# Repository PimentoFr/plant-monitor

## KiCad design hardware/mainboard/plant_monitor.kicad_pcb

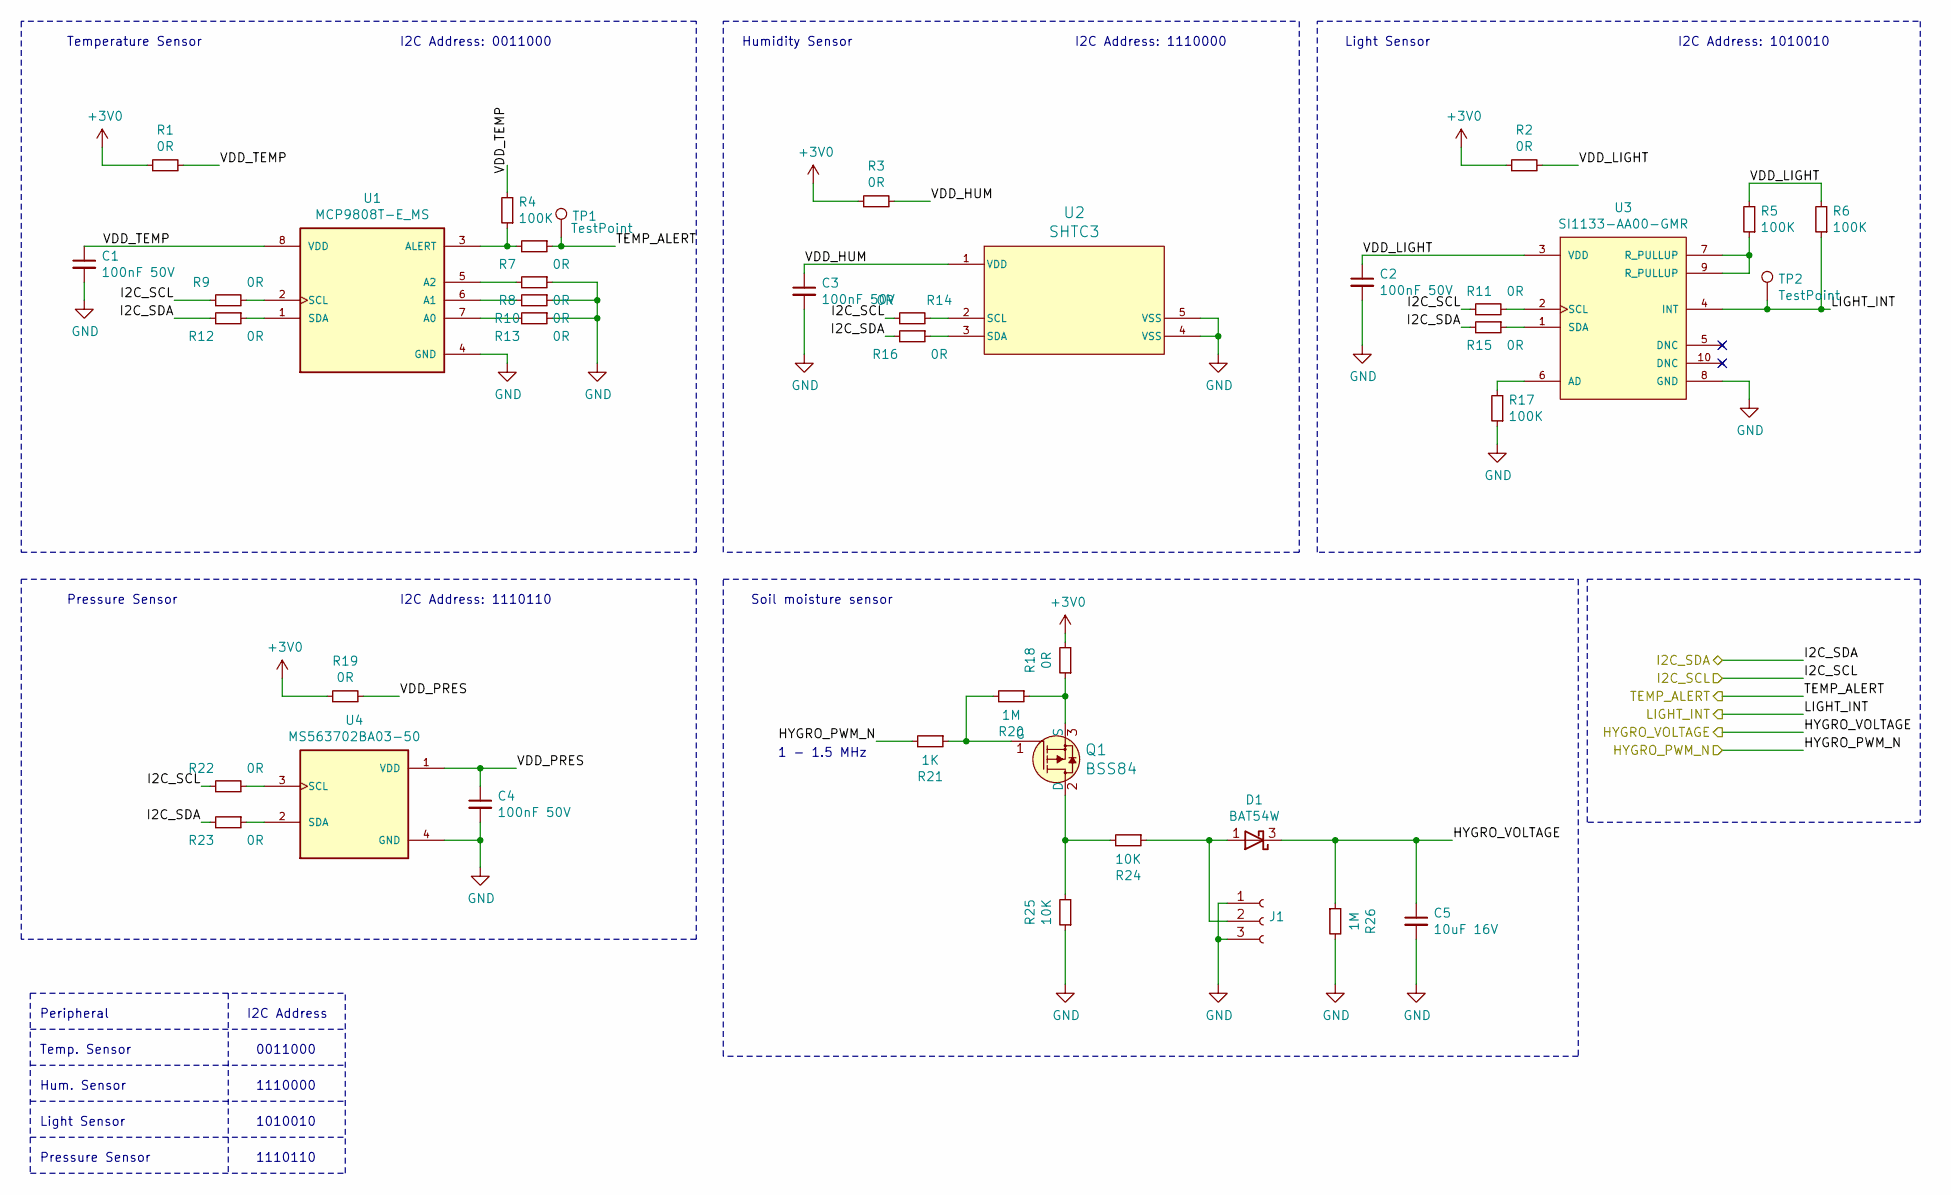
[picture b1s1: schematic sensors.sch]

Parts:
C1, C2, C3, C4: 100nF 50V; C_0402_1005Metric
C5: 10uF 16V; C_0805_2012Metric_Pad1.15x1.40mm_HandSolder; farnell 3013487
D1: BAT54W; SOT-323_SC-70; farnell 1081197
J1: Conn_01x03_Female; PinSocket_1x03_P2.54mm_Vertical
Q1: BSS84; SOT-23-3; MPN BSS84; Digi-Key_PN BSS84CT-ND
R1, R2, R3, R7, R8, R9, R10, R11, R12, R13, R14, R15, R16, R18, R19, R22, R23: 0R; R_0402_1005Metric
R4, R5, R6, R17: 100K; R_0402_1005Metric
R20, R26: 1M; R_0402_1005Metric
R21: 1K; R_0402_1005Metric
R24, R25: 10K; R_0402_1005Metric
TP1, TP2: TestPoint; TestPoint_Pad_D1.0mm
U1: MCP9808T-E_MS; SOP65P490X110-8N; farnell 2851677
U2: SHTC3; farnell 3106918
U3: SI1133-AA00-GMR; farnell 3105966
U4: MS563702BA03-50; TE_MS563702BA03-50; farnell 2362663

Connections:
+3V0: R1.1, R2.1, R3.1, R18.2, R19.1; also elsewhere on the board
/mcu/HYGRO_PWM_N: R21.2; also elsewhere on the board
/mcu/HYGRO_VOLTAGE: C5.1, D1.3 (K), R26.1; also elsewhere on the board
/mcu/I2C_SCL: R9.1, R11.1, R14.1, R22.1; also elsewhere on the board
/mcu/I2C_SDA: R12.2, R15.2, R16.2, R23.2; also elsewhere on the board
/mcu/LIGHT_INT: R6.1, TP2.1, U3.4 (INT); also elsewhere on the board
/mcu/TEMP_ALERT: R7.1, TP1.1; also elsewhere on the board
/sensors/VDD_HUM: C3.1, R3.2, U2.1 (VDD)
/sensors/VDD_LIGHT: C2.1, R2.2, R5.2, R6.2, U3.3 (VDD)
/sensors/VDD_PRES: C4.1, R19.2, U4.1 (VDD)
/sensors/VDD_TEMP: C1.1, R1.2, R4.2, U1.8 (VDD)
GND: C1.2, C2.2, C3.2, C4.2, C5.2, J1.1, J1.3, R8.1, R10.1, R13.1, R17.1, R25.1, R26.2, U1.4 (GND), U2.4 (VSS), U2.5 (VSS), U3.8 (GND), U4.4 (GND); also elsewhere on the board
unnamed: D1.1 (A), J1.2, R24.1
unnamed: Q1.1 (G), R20.2, R21.1
unnamed: Q1.2 (D), R24.2, R25.2
unnamed: Q1.3 (S), R18.1, R20.1
unnamed: R4.1, R7.2, U1.3 (ALERT)
unnamed: R5.1, U3.7 (R_PULLUP), U3.9 (R_PULLUP)
unnamed: R8.2, U1.5 (A2)
unnamed: R9.2, U1.2 (SCL)
unnamed: R10.2, U1.6 (A1)
unnamed: R11.2, U3.2 (SCL)
unnamed: R12.1, U1.1 (SDA)
unnamed: R13.2, U1.7 (A0)
unnamed: R14.2, U2.2 (SCL)
unnamed: R15.1, U3.1 (SDA)
unnamed: R16.1, U2.3 (SDA)
unnamed: R17.2, U3.6 (AD)
unnamed: R22.2, U4.3 (SCL)
unnamed: R23.1, U4.2 (SDA)

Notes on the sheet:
Temperature Sensor
I2C Address: 0011000
I2C Address
Peripheral
Temp. Sensor
0011000
Humidity Sensor
I2C Address: 1110000
Hum. Sensor
1110000
Light Sensor
I2C Address: 1010010
1010010
Pressure Sensor
I2C Address: 1110110
1110110
Soil moisture sensor
1 - 1.5 MHz

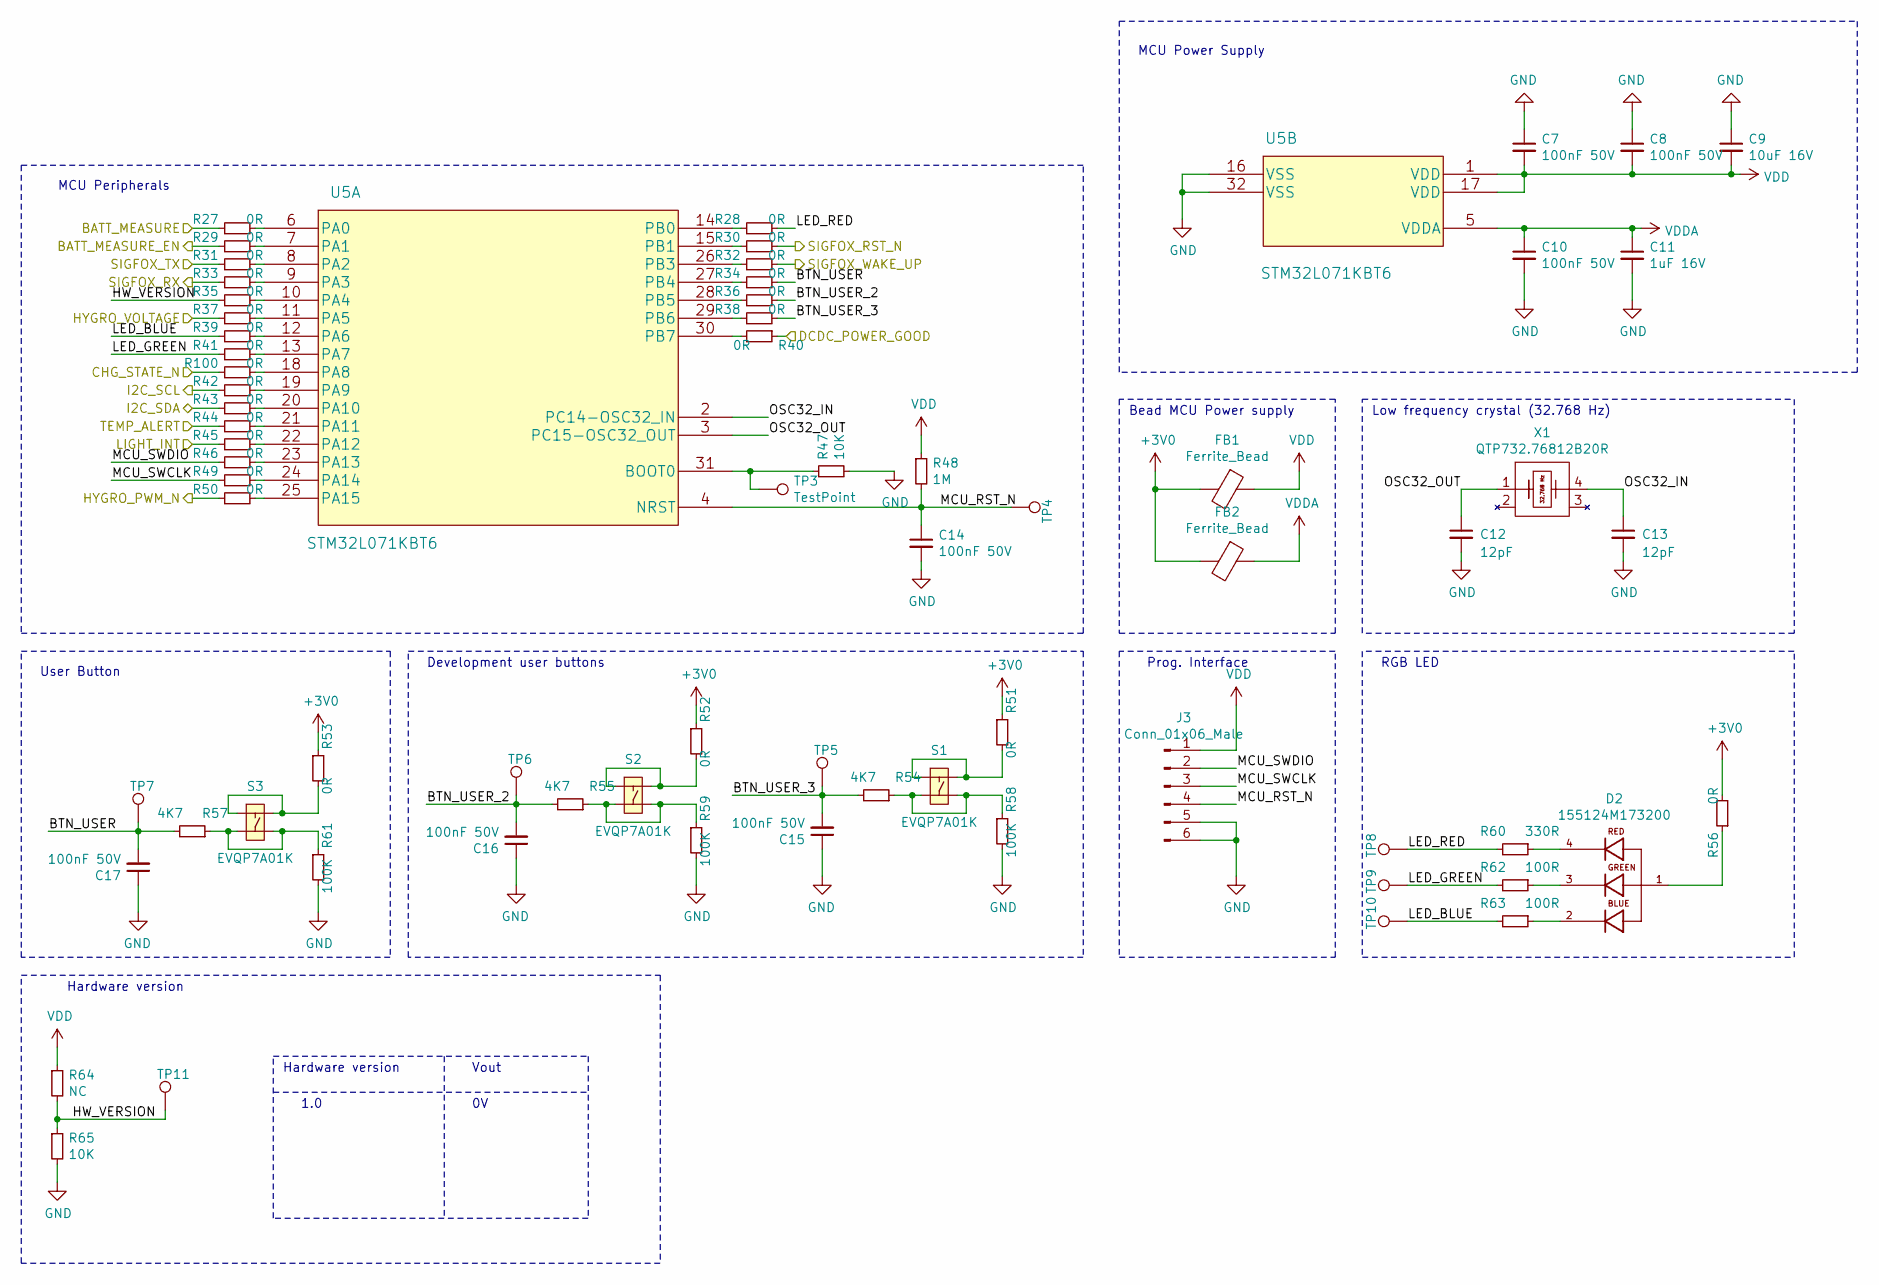
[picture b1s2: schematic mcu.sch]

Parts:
C7, C8, C10, C14, C15, C16, C17: 100nF 50V; C_0402_1005Metric
C9: 10uF 16V; C_0805_2012Metric_Pad1.15x1.40mm_HandSolder; farnell 3013487
C11: 1uF 16V; C_0603_1608Metric; farnell 3013385
C12, C13: 12pF; C_0402_1005Metric
D2: 155124M173200; LED_155124M173200; PARTREV 001.000; farnell 2764995
FB1, FB2: Ferrite_Bead; R_0402_1005Metric
J3: Conn_01x06_Male; PinHeader_1x06_P2.54mm_Vertical; farnell 1593415
R27, R28, R29, R30, R31, R32, R33, R34, R35, R36, R37, R38, R39, R40, R41, R42, R43, R44, R45, R46, R49, R50, R51, R52, R53, R56, R100: 0R; R_0402_1005Metric
R47, R65: 10K; R_0402_1005Metric
R48: 1M; R_0402_1005Metric
R54, R55, R57: 4K7; R_0402_1005Metric
R58, R59, R61: 100K; R_0402_1005Metric
R60: 330R; R_0402_1005Metric
R62, R63: 100R; R_0402_1005Metric
R64: NC; R_0402_1005Metric
S1, S2, S3: EVQP7A01K; farnell 2079538
TP3, TP4, TP5, TP6, TP7, TP8, TP9, TP10, TP11: TestPoint; TestPoint_Pad_D1.0mm
U5: STM32L071KBT6; farnell 3365397
X1: QTP732.76812B20R; farnell 2508436

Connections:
+3V0: FB1.2, FB2.2, R51.1, R52.1, R53.1, R56.2; also elsewhere on the board
/mcu/BATT_MEASURE: R27.1; also elsewhere on the board
/mcu/BATT_MEASURE_EN: R29.1; also elsewhere on the board
/mcu/BTN_USER: C17.2, R34.2, R57.2, TP7.1
/mcu/BTN_USER_2: C16.2, R36.2, R55.2, TP6.1
/mcu/BTN_USER_3: C15.2, R38.2, R54.2, TP5.1
/mcu/CHG_STATE_N: R100.1; also elsewhere on the board
/mcu/DCDC_POWER_GOOD: R40.1; also elsewhere on the board
/mcu/HW_VERSION: R35.1, R64.2, R65.1, TP11.1
/mcu/HYGRO_PWM_N: R50.1; also elsewhere on the board
/mcu/HYGRO_VOLTAGE: R37.1; also elsewhere on the board
/mcu/I2C_SCL: R42.1; also elsewhere on the board
/mcu/I2C_SDA: R43.1; also elsewhere on the board
/mcu/LED_BLUE: R39.1, R63.2, TP10.1
/mcu/LED_GREEN: R41.1, R62.2, TP9.1
/mcu/LED_RED: R28.2, R60.2, TP8.1
/mcu/LIGHT_INT: R45.1; also elsewhere on the board
/mcu/MCU_RST_N: C14.1, J3.4, R48.2, TP4.1, U5.4 (NRST)
/mcu/MCU_SWCLK: J3.3, R49.1
/mcu/MCU_SWDIO: J3.2, R46.1
/mcu/OSC32_IN: C13.1, U5.2 (PC14-OSC32_IN), X1.4
/mcu/OSC32_OUT: C12.1, U5.3 (PC15-OSC32_OUT), X1.1
/mcu/SIGFOX_RST_N: R30.2; also elsewhere on the board
/mcu/SIGFOX_RX: R33.1; also elsewhere on the board
/mcu/SIGFOX_TX: R31.1; also elsewhere on the board
/mcu/SIGFOX_WAKE_UP: R32.2; also elsewhere on the board
/mcu/TEMP_ALERT: R44.1; also elsewhere on the board
GND: C7.1, C8.1, C9.1, C10.2, C11.2, C12.2, C13.2, C14.2, C15.1, C16.1, C17.1, J3.5, J3.6, R47.2, R58.2, R59.2, R61.2, R65.2, U5.16 (VSS), U5.32 (VSS); also elsewhere on the board
unnamed: D2.1, R56.1
unnamed: D2.2, R63.1
unnamed: D2.3, R62.1
unnamed: D2.4, R60.1
unnamed: R27.2, U5.6 (PA0)
unnamed: R28.1, U5.14 (PB0)
unnamed: R29.2, U5.7 (PA1)
unnamed: R30.1, U5.15 (PB1)
unnamed: R31.2, U5.8 (PA2)
unnamed: R32.1, U5.26 (PB3)
unnamed: R33.2, U5.9 (PA3)
unnamed: R34.1, U5.27 (PB4)
unnamed: R35.2, U5.10 (PA4)
unnamed: R36.1, U5.28 (PB5)
unnamed: R37.2, U5.11 (PA5)
unnamed: R38.1, U5.29 (PB6)
unnamed: R39.2, U5.12 (PA6)
unnamed: R40.2, U5.30 (PB7)
unnamed: R41.2, U5.13 (PA7)
unnamed: R42.2, U5.19 (PA9)
unnamed: R43.2, U5.20 (PA10)
unnamed: R44.2, U5.21 (PA11)
unnamed: R45.2, U5.22 (PA12)
unnamed: R46.2, U5.23 (PA13)
unnamed: R47.1, TP3.1, U5.31 (BOOT0)
unnamed: R49.2, U5.24 (PA14)
unnamed: R50.2, U5.25 (PA15)
unnamed: R51.2, S1.1, S1.4
unnamed: R52.2, S2.1, S2.4
unnamed: R53.2, S3.1, S3.4
unnamed: R54.1, R58.1, S1.2, S1.3
unnamed: R55.1, R59.1, S2.2, S2.3
unnamed: R57.1, R61.1, S3.2, S3.3
unnamed: R100.2, U5.18 (PA8)
VDD: C7.2, C8.2, C9.2, FB1.1, J3.1, R48.1, R64.1, U5.1 (VDD), U5.17 (VDD)
VDDA: C10.1, C11.1, FB2.1, U5.5 (VDDA)

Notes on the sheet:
Hardware version
Vout
1.0
RGB LED
Low frequency crystal (32.768 Hz)
User Button
Development user buttons
MCU Peripherals
MCU Power Supply
Prog. Interface
Bead MCU Power supply

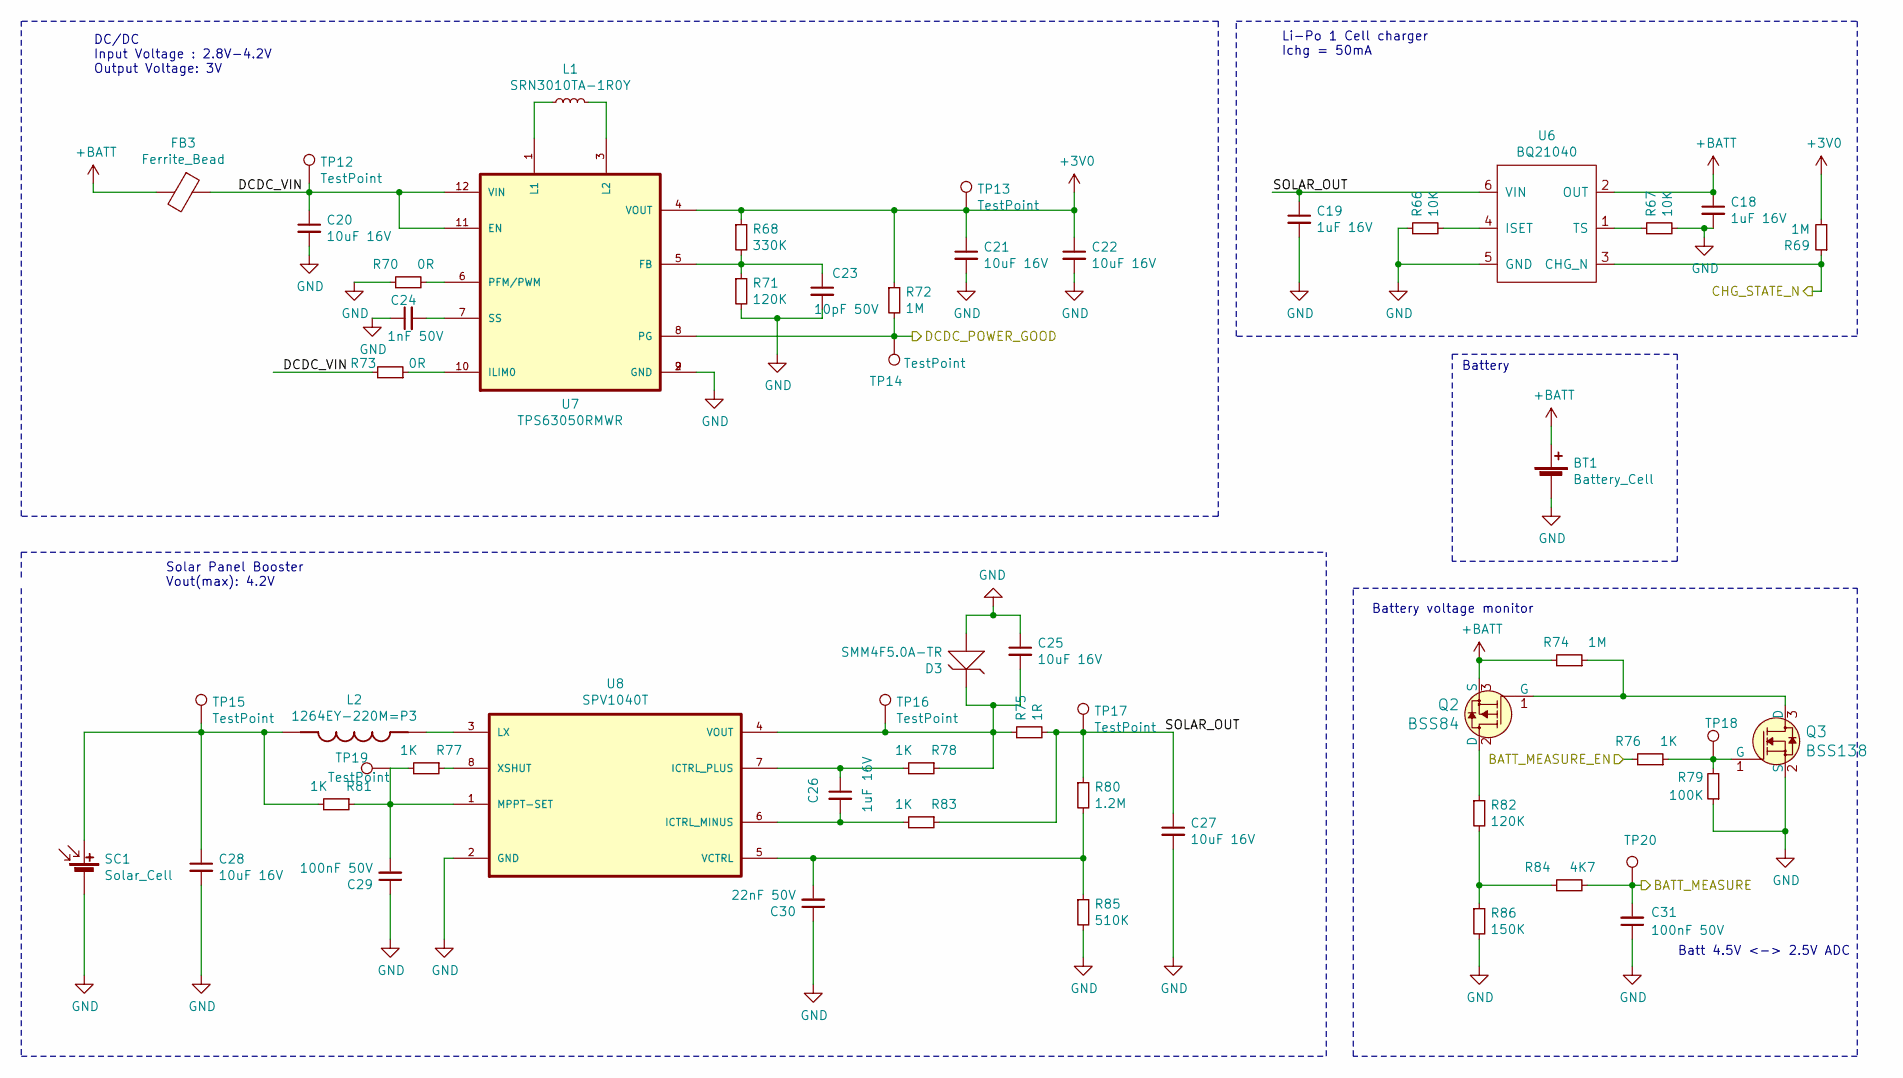
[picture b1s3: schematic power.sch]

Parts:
BT1: Battery_Cell; JST_PH_S2B-PH-K_1x02_P2.00mm_Horizontal
C18, C19, C26: 1uF 16V; C_0603_1608Metric; farnell 3013385
C20, C21, C22, C25, C27, C28: 10uF 16V; C_0805_2012Metric_Pad1.15x1.40mm_HandSolder; farnell 3013487
C23: 10pF 50V; C_0402_1005Metric
C24: 1nF 50V; C_0402_1005Metric
C29, C31: 100nF 50V; C_0402_1005Metric
C30: 22nF 50V; C_0402_1005Metric
D3: SMM4F5.0A-TR; farnell 1689313
FB3: Ferrite_Bead; R_0402_1005Metric
L1: SRN3010TA-1R0Y; SRN3010TA; farnell 2808286
L2: 1264EY-220M=P3; IND_1264EY-220M=P3; PARTREV N/A; farnell 2871571
Q2: BSS84; SOT-23-3; MPN BSS84; Digi-Key_PN BSS84CT-ND
Q3: BSS138; SOT-23-3; MPN BSS138; Digi-Key_PN BSS138CT-ND
R66, R67: 10K; R_0402_1005Metric
R68: 330K; R_0402_1005Metric
R69, R72, R74: 1M; R_0402_1005Metric
R70, R73: 0R; R_0402_1005Metric
R71, R82: 120K; R_0402_1005Metric
R75: 1R; R_0402_1005Metric
R76, R77, R78, R81, R83: 1K; R_0402_1005Metric
R79: 100K; R_0402_1005Metric
R80: 1.2M; R_0402_1005Metric
R84: 4K7; R_0402_1005Metric
R85: 510K; R_0402_1005Metric
R86: 150K; R_0402_1005Metric
SC1: Solar_Cell; SOLAR_CELL
TP12, TP13, TP14, TP15, TP16, TP17, TP18, TP19, TP20: TestPoint; TestPoint_Pad_D1.0mm
U6: BQ21040; SOT-23-6
U7: TPS63050RMWR; QFN50P250X250X100-12N; farnell 3007462
U8: SPV1040T; SOP65P640X120-8N; PARTREV 7; farnell 2762710

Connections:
+3V0: C21.1, C22.1, R68.1, R69.2, R72.1, TP13.1, U7.4 (VOUT); also elsewhere on the board
+BATT: BT1.1 (+), C18.1, FB3.2, Q2.3 (S), R74.2, U6.2 (OUT)
/mcu/BATT_MEASURE: C31.2, R84.2, TP20.1; also elsewhere on the board
/mcu/BATT_MEASURE_EN: R76.2; also elsewhere on the board
/mcu/CHG_STATE_N: R69.1, U6.3 (CHG_N); also elsewhere on the board
/mcu/DCDC_POWER_GOOD: R72.2, TP14.1, U7.8 (PG); also elsewhere on the board
/power/DCDC_VIN: C20.1, FB3.1, R73.2, TP12.1, U7.11 (EN), U7.12 (VIN)
/power/SOLAR_OUT: C19.1, C27.1, R75.2, R80.1, R83.1, TP17.1, U6.6 (VIN)
GND: BT1.2 (-), C18.2, C19.2, C20.2, C21.2, C22.2, C23.2, C24.1, C25.1, C27.2, C28.2, C29.1, C30.1, C31.1, D3.A, Q3.2 (S), R66.1, R67.2, R70.1, R71.2, R79.1, R85.2, R86.2, SC1.2 (-), U6.5 (GND), U7.2 (GND), U7.9 (GND), U8.2 (GND); also elsewhere on the board
unnamed: C23.1, R68.2, R71.1, U7.5 (FB)
unnamed: C24.2, U7.7 (SS)
unnamed: C25.2, D3.K, R75.1, R78.1, TP16.1, U8.4 (VOUT)
unnamed: C26.1, R78.2, U8.7 (ICTRL_PLUS)
unnamed: C26.2, R83.2, U8.6 (ICTRL_MINUS)
unnamed: C28.1, L2.1, R81.2, SC1.1 (+), TP15.1
unnamed: C29.2, R77.2, R81.1, TP19.1, U8.1 (MPPT-SET)
unnamed: C30.2, R80.2, R85.1, U8.5 (VCTRL)
unnamed: L1.1, U7.1 (L1)
unnamed: L1.2, U7.3 (L2)
unnamed: L2.2, U8.3 (LX)
unnamed: Q2.1 (G), Q3.3 (D), R74.1
unnamed: Q2.2 (D), R82.1
unnamed: Q3.1 (G), R76.1, R79.2, TP18.1
unnamed: R66.2, U6.4 (ISET)
unnamed: R67.1, U6.1 (TS)
unnamed: R70.2, U7.6 (PFM/PWM)
unnamed: R73.1, U7.10 (ILIM0)
unnamed: R77.1, U8.8 (XSHUT)
unnamed: R82.2, R84.1, R86.1

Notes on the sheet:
DC/DC Input Voltage : 2.8V-4.2V Output Voltage: 3V
Solar Panel Booster Vout(max): 4.2V
Li-Po 1 Cell charger Ichg = 50mA
Battery
Battery voltage monitor
Batt 4.5V <-> 2.5V ADC

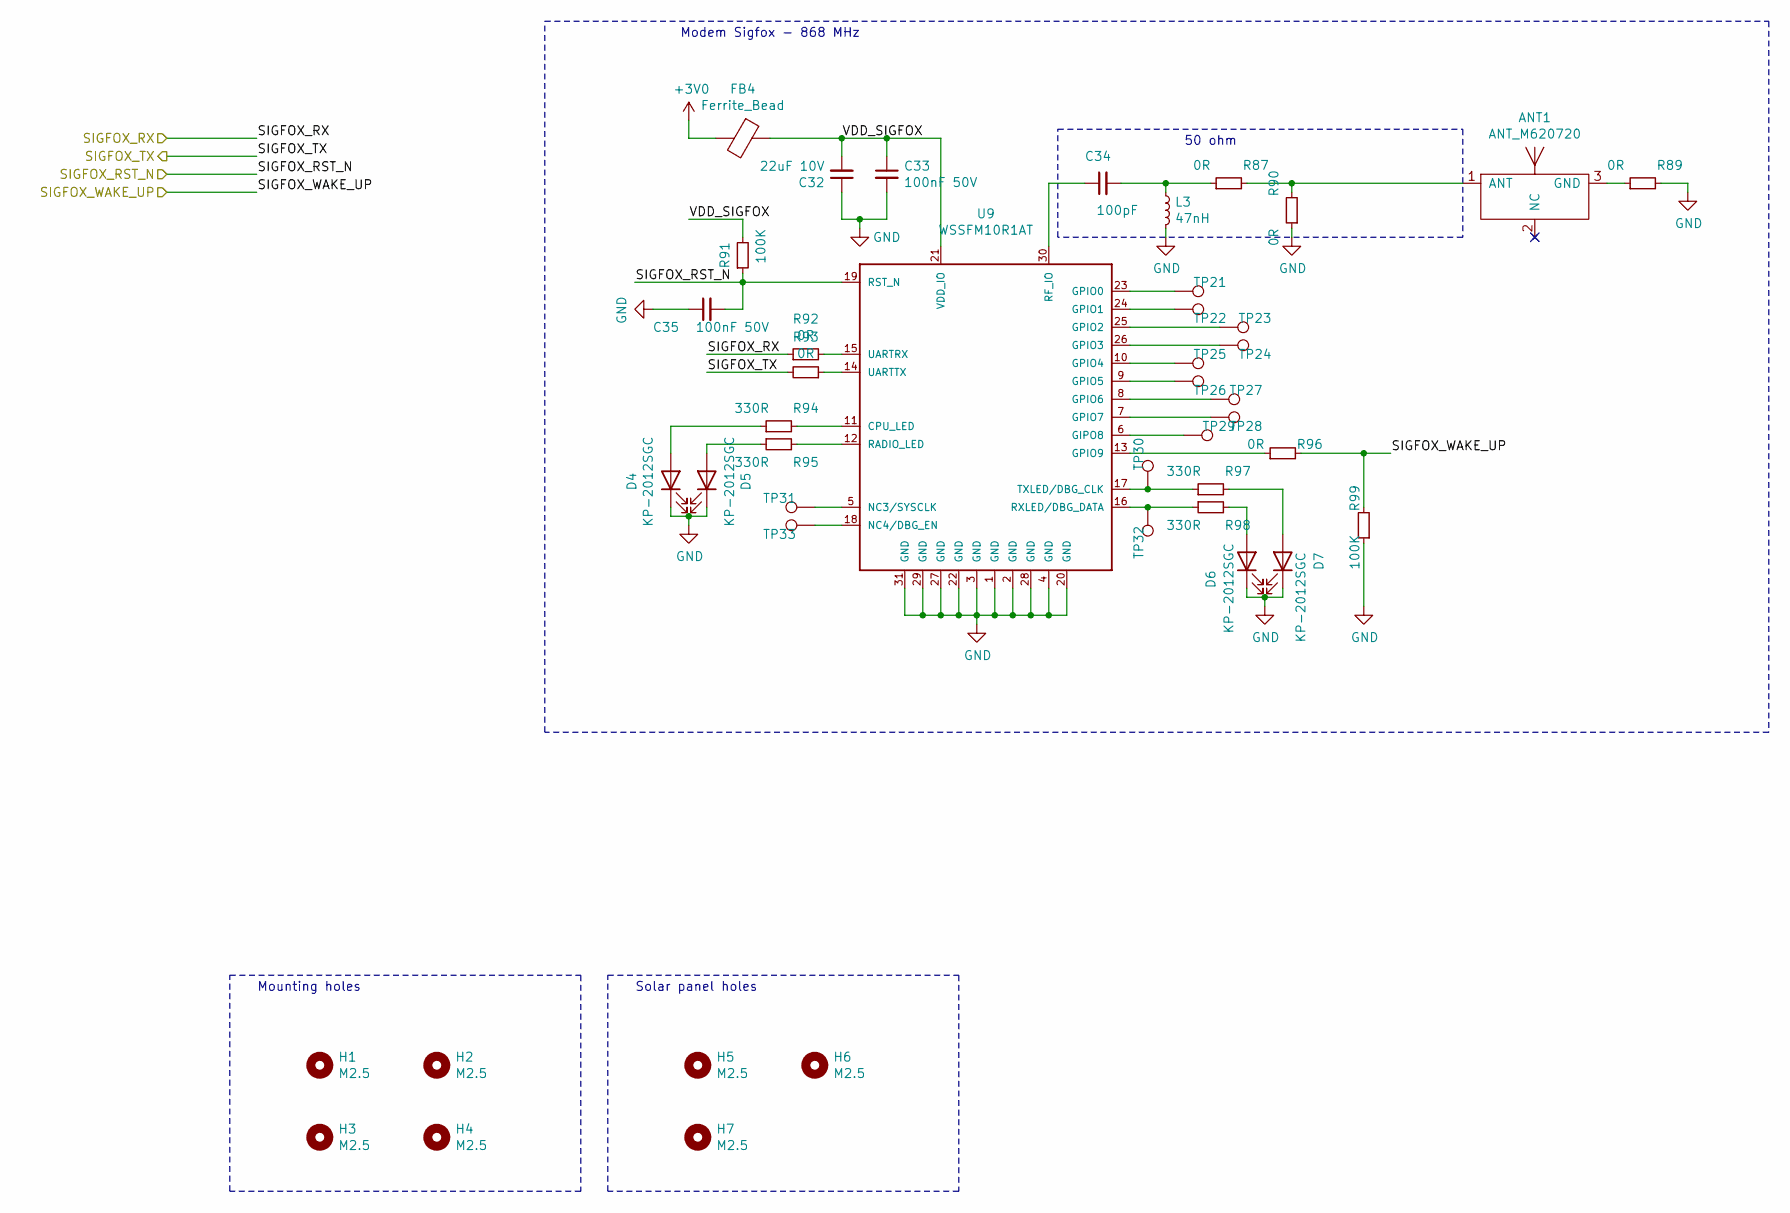
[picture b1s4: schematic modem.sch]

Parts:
ANT1: ANT_M620720; M620720; digikey 939-1066-1-ND
C32: 22uF 10V; C_0805_2012Metric_Pad1.15x1.40mm_HandSolder; farnell 2494270
C33, C35: 100nF 50V; C_0402_1005Metric
C34: 100pF; C_0402_1005Metric
D4, D5, D6, D7: KP-2012SGC; farnell 1318243
FB4: Ferrite_Bead; R_0402_1005Metric
H1, H2, H3, H4, H5, H6, H7: M2.5; MountingHole_2.7mm_M2.5
L3: 47nH; L_0402_1005Metric
R87, R89, R90, R92, R93, R96: 0R; R_0402_1005Metric
R91, R99: 100K; R_0402_1005Metric
R94, R95, R97, R98: 330R; R_0402_1005Metric
TP21, TP22, TP23, TP24, TP25, TP26, TP27, TP28, TP29, TP30, TP31, TP32, TP33: TestPoint; TestPoint_Pad_D1.0mm
U9: WSSFM10R1AT; XCVR_WSSFM10R1AT_HANDSOLDER

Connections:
+3V0: FB4.2; also elsewhere on the board
/mcu/SIGFOX_RST_N: C35.2, R91.1, U9.19 (RST_N); also elsewhere on the board
/mcu/SIGFOX_RX: R92.1; also elsewhere on the board
/mcu/SIGFOX_TX: R93.2; also elsewhere on the board
/mcu/SIGFOX_WAKE_UP: R96.2, R99.2; also elsewhere on the board
/modem/VDD_SIGFOX: C32.2, C33.1, FB4.1, R91.2, U9.21 (VDD_IO)
GND: C32.1, C33.2, C35.1, D4.1 (K), D5.1 (K), D6.1 (K), D7.1 (K), L3.2, R89.2, R90.1, R99.1, U9.1 (GND), U9.2 (GND), U9.3 (GND), U9.4 (GND), U9.20 (GND), U9.22 (GND), U9.27 (GND), U9.28 (GND), U9.29 (GND), U9.31 (GND); also elsewhere on the board
unnamed: ANT1.1 (ANT), R87.2, R90.2
unnamed: ANT1.3 (GND), R89.1
unnamed: C34.1, U9.30 (RF_IO)
unnamed: C34.2, L3.1, R87.1
unnamed: D4.2 (A), R94.1
unnamed: D5.2 (A), R95.1
unnamed: D6.2 (A), R98.2
unnamed: D7.2 (A), R97.2
unnamed: R92.2, U9.15 (UARTRX)
unnamed: R93.1, U9.14 (UARTTX)
unnamed: R94.2, U9.11 (CPU_LED)
unnamed: R95.2, U9.12 (RADIO_LED)
unnamed: R96.1, U9.13 (GPIO9)
unnamed: R97.1, TP30.1, U9.17 (TXLED/DBG_CLK)
unnamed: R98.1, TP32.1, U9.16 (RXLED/DBG_DATA)
unnamed: TP21.1, U9.23 (GPIO0)
unnamed: TP22.1, U9.24 (GPIO1)
unnamed: TP23.1, U9.25 (GPIO2)
unnamed: TP24.1, U9.26 (GPIO3)
unnamed: TP25.1, U9.10 (GPIO4)
unnamed: TP26.1, U9.9 (GPIO5)
unnamed: TP27.1, U9.8 (GPIO6)
unnamed: TP28.1, U9.7 (GPIO7)
unnamed: TP29.1, U9.6 (GIPO8)
unnamed: TP31.1, U9.5 (NC3/SYSCLK)
unnamed: TP33.1, U9.18 (NC4/DBG_EN)

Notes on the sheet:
Modem Sigfox - 868 MHz
50 ohm
Mounting holes
Solar panel holes

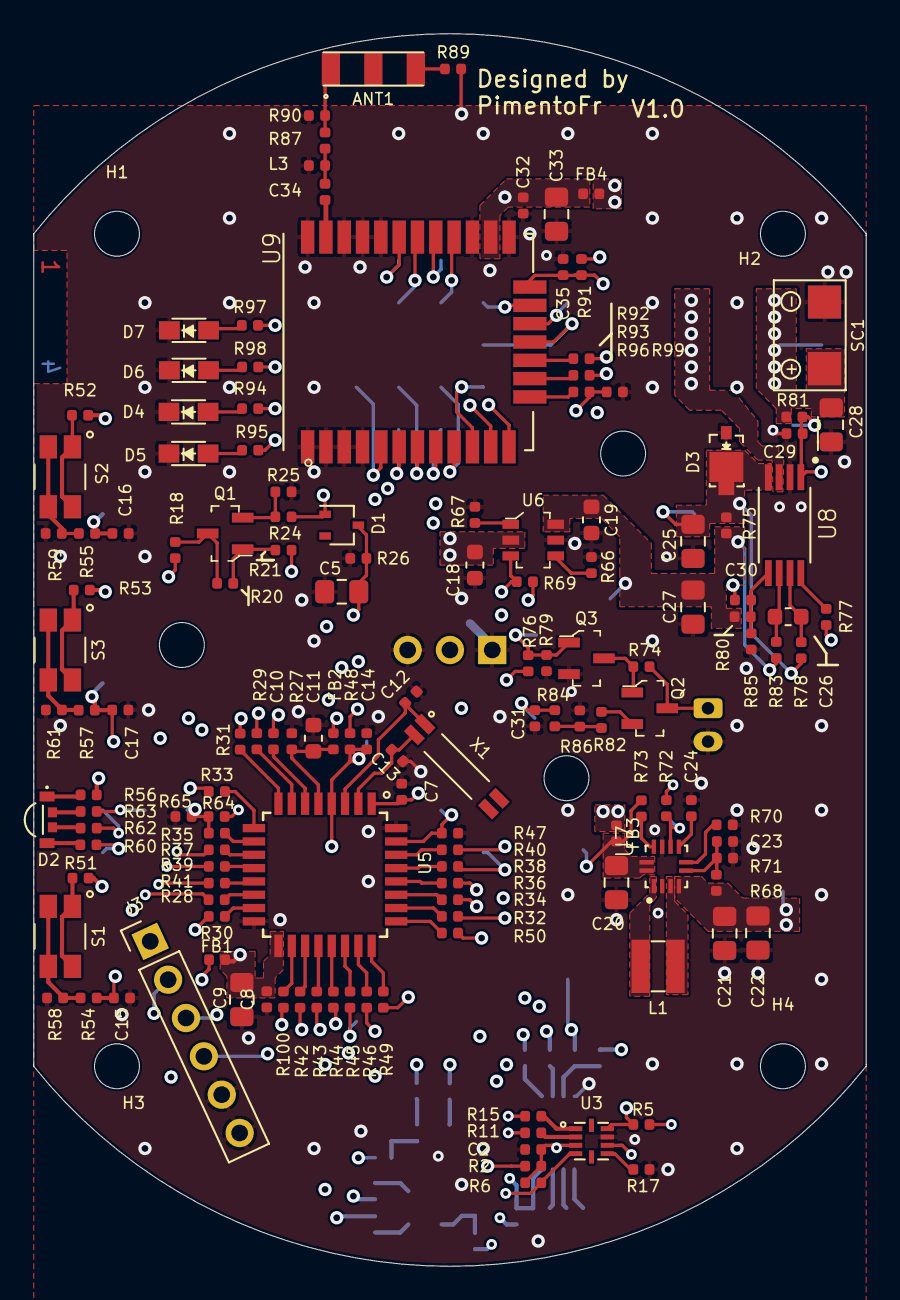
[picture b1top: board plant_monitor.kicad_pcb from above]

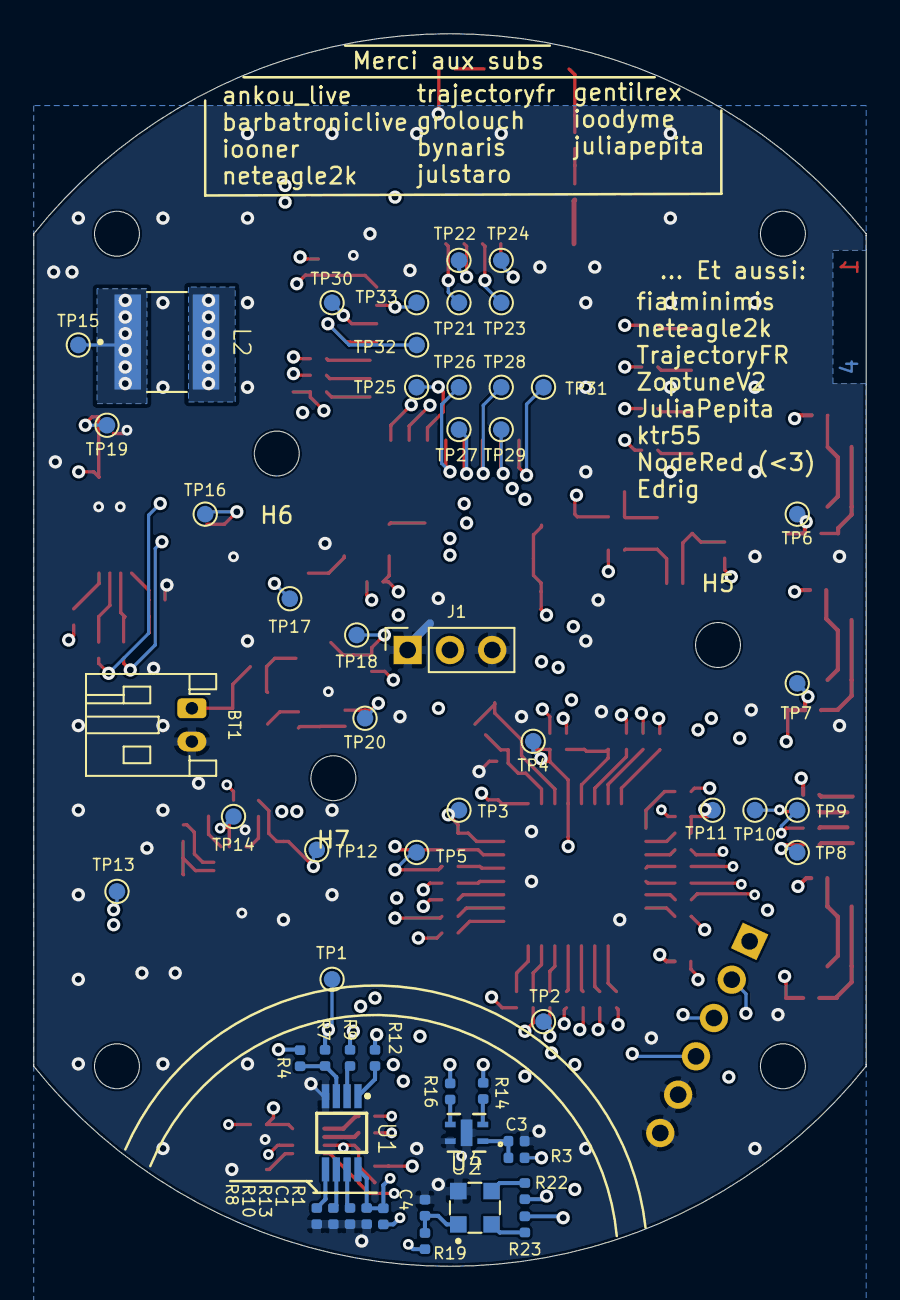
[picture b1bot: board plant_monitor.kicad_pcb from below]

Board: 4 copper layers, 50.0 x 74.0 mm, 208 parts (58 on the bottom side), 136 nets.

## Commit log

2021-02-06 wip 2
2021-02-21 plant monitor
2021-02-24 wip: casing for the mainboard

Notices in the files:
parts and their libraries:
Copyright 2016 Accelerated Designs. All rights reserved.
